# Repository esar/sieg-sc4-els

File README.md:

# sieg-sc4-els
SIEG SC4 Electronic Lead Screw

This is an electronic lead screw controller designed for the SIEG SC4 lathe, though it would also work fine for others.

This repo contains the Kicad files for the controller PCB and the firmware.

See https://hacks.esar.org.uk/sieg-sc4-electronic-lead-screw/ for more details

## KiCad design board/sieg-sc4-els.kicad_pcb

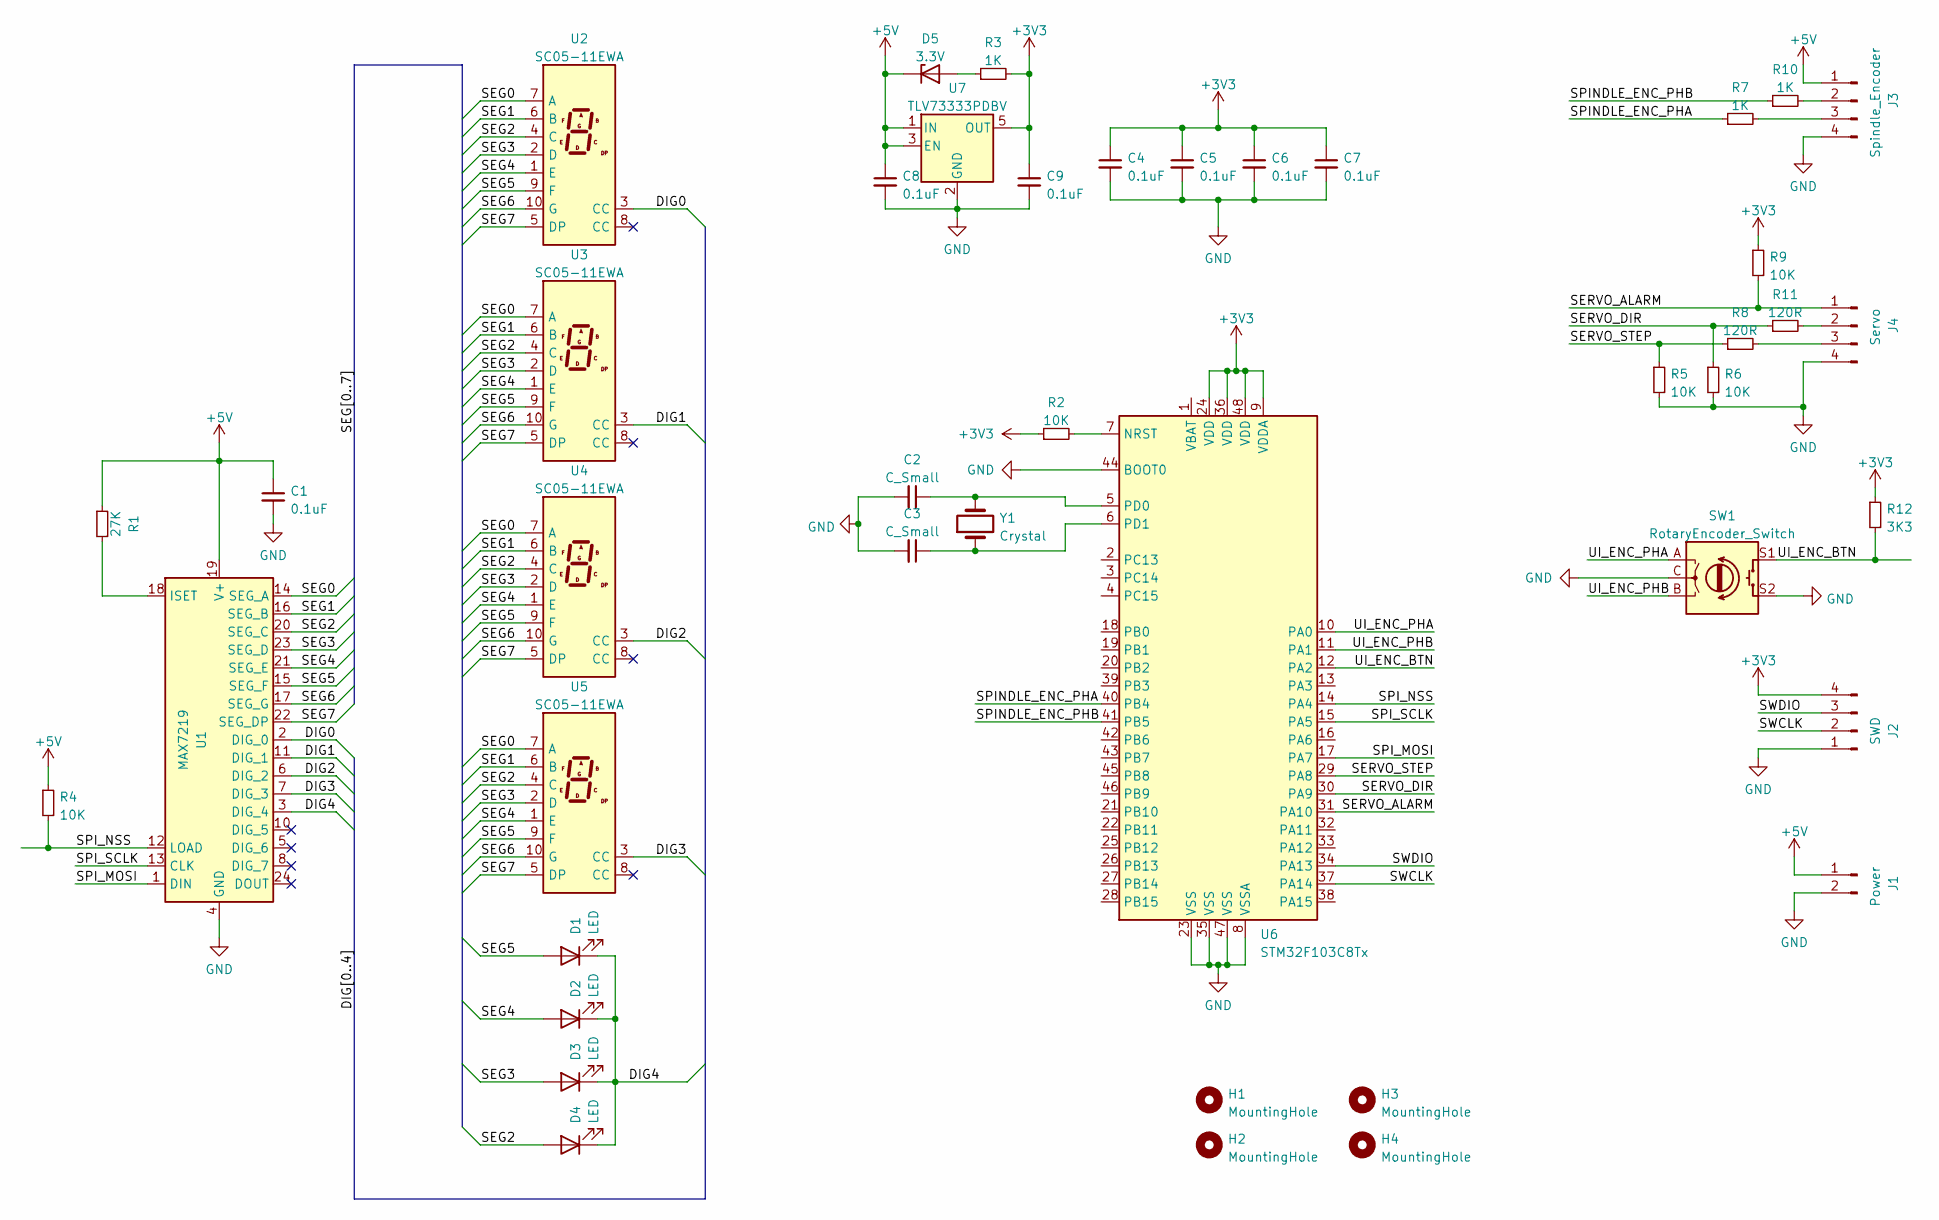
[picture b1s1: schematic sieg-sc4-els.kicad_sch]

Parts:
C1, C4, C5, C6, C7, C8, C9: 0.1uF; C_0603_1608Metric
C2, C3: C_Small; C_0603_1608Metric
D1, D2, D3, D4: LED; LED_D3.0mm
D5: 3.3V; D_SOD-323
H1, H2, H3, H4: MountingHole; MountingHole_3.2mm_M3
J1: Power; JST_XH_B2B-XH-A_1x02_P2.50mm_Vertical
J2: SWD; JST_XH_B4B-XH-A_1x04_P2.50mm_Vertical
J3: Spindle_Encoder; JST_XH_B4B-XH-A_1x04_P2.50mm_Vertical
J4: Servo; JST_XH_B4B-XH-A_1x04_P2.50mm_Vertical
R1: 27K; R_0603_1608Metric
R2, R4, R5, R6, R9: 10K; R_0603_1608Metric
R3, R7, R10: 1K; R_0603_1608Metric
R8, R11: 120R; R_0603_1608Metric
R12: 3K3; R_0603_1608Metric
SW1: RotaryEncoder_Switch; RotaryEncoder_Alps_EC11E-Switch_Vertical_H20mm
U1: MAX7219; SOIC-24W_7.5x15.4mm_P1.27mm
U2, U3, U4, U5: SC05-11EWA; D1X8K
U6: STM32F103C8Tx; LQFP-48_7x7mm_P0.5mm
U7: TLV73333PDBV; SOT-23-5
Y1: Crystal; Crystal_SMD_SeikoEpson_MA505-2Pin_12.7x5.1mm

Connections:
+3V3: C4.1, C5.1, C6.1, C7.1, C9.1, J2.4, R2.1, R3.2, R9.1, R12.1, U6.9 (VDDA), U6.24 (VDD), U6.36 (VDD), U6.48 (VDD), U7.5 (OUT)
+5V: C1.1, C8.1, D5.1 (K), J1.1, J3.1, R1.1, R4.1, U1.19 (V+), U7.1 (IN), U7.3 (EN)
/DIG0: U1.2 (DIG_0), U2.3 (CC)
/DIG1: U1.11 (DIG_1), U3.3 (CC)
/DIG2: U1.6 (DIG_2), U4.3 (CC)
/DIG3: U1.7 (DIG_3), U5.3 (CC)
/DIG4: D1.1 (K), D2.1 (K), D3.1 (K), D4.1 (K), U1.3 (DIG_4)
/SEG0: U1.14 (SEG_A), U2.7 (A), U3.7 (A), U4.7 (A), U5.7 (A)
/SEG1: U1.16 (SEG_B), U2.6 (B), U3.6 (B), U4.6 (B), U5.6 (B)
/SEG2: D4.2 (A), U1.20 (SEG_C), U2.4 (C), U3.4 (C), U4.4 (C), U5.4 (C)
/SEG3: D3.2 (A), U1.23 (SEG_D), U2.2 (D), U3.2 (D), U4.2 (D), U5.2 (D)
/SEG4: D2.2 (A), U1.21 (SEG_E), U2.1 (E), U3.1 (E), U4.1 (E), U5.1 (E)
/SEG5: D1.2 (A), U1.15 (SEG_F), U2.9 (F), U3.9 (F), U4.9 (F), U5.9 (F)
/SEG6: U1.17 (SEG_G), U2.10 (G), U3.10 (G), U4.10 (G), U5.10 (G)
/SEG7: U1.22 (SEG_DP), U2.5 (DP), U3.5 (DP), U4.5 (DP), U5.5 (DP)
/SERVO_ALARM: J4.1, R9.2, U6.31 (PA10)
/SERVO_DIR: R6.1, R11.1, U6.30 (PA9)
/SERVO_STEP: R5.1, R8.1, U6.29 (PA8)
/SPINDLE_ENC_PHA: R7.1, U6.40 (PB4)
/SPINDLE_ENC_PHB: R10.1, U6.41 (PB5)
/SPI_MOSI: U1.1 (DIN), U6.17 (PA7)
/SPI_NSS: R4.2, U1.12 (LOAD), U6.14 (PA4)
/SPI_SCLK: U1.13 (CLK), U6.15 (PA5)
/SWCLK: J2.2, U6.37 (PA14)
/SWDIO: J2.3, U6.34 (PA13)
/UI_ENC_BTN: R12.2, SW1.S1, U6.12 (PA2)
/UI_ENC_PHA: SW1.A, U6.10 (PA0)
/UI_ENC_PHB: SW1.B, U6.11 (PA1)
GND: C1.2, C2.2, C3.2, C4.2, C5.2, C6.2, C7.2, C8.2, C9.2, J1.2, J2.1, J3.4, J4.4, R5.2, R6.2, SW1.C, SW1.S2, U1.4 (GND), U1.9 (GND), U6.8 (VSSA), U6.23 (VSS), U6.35 (VSS), U6.44 (BOOT0), U6.47 (VSS), U7.2 (GND)
unnamed: C2.1, U6.5 (PD0), Y1.2
unnamed: C3.1, U6.6 (PD1), Y1.1
unnamed: D5.2 (A), R3.1
unnamed: J3.2, R10.2
unnamed: J3.3, R7.2
unnamed: J4.2, R11.2
unnamed: J4.3, R8.2
unnamed: R1.2, U1.18 (ISET)
unnamed: R2.2, U6.7 (NRST)

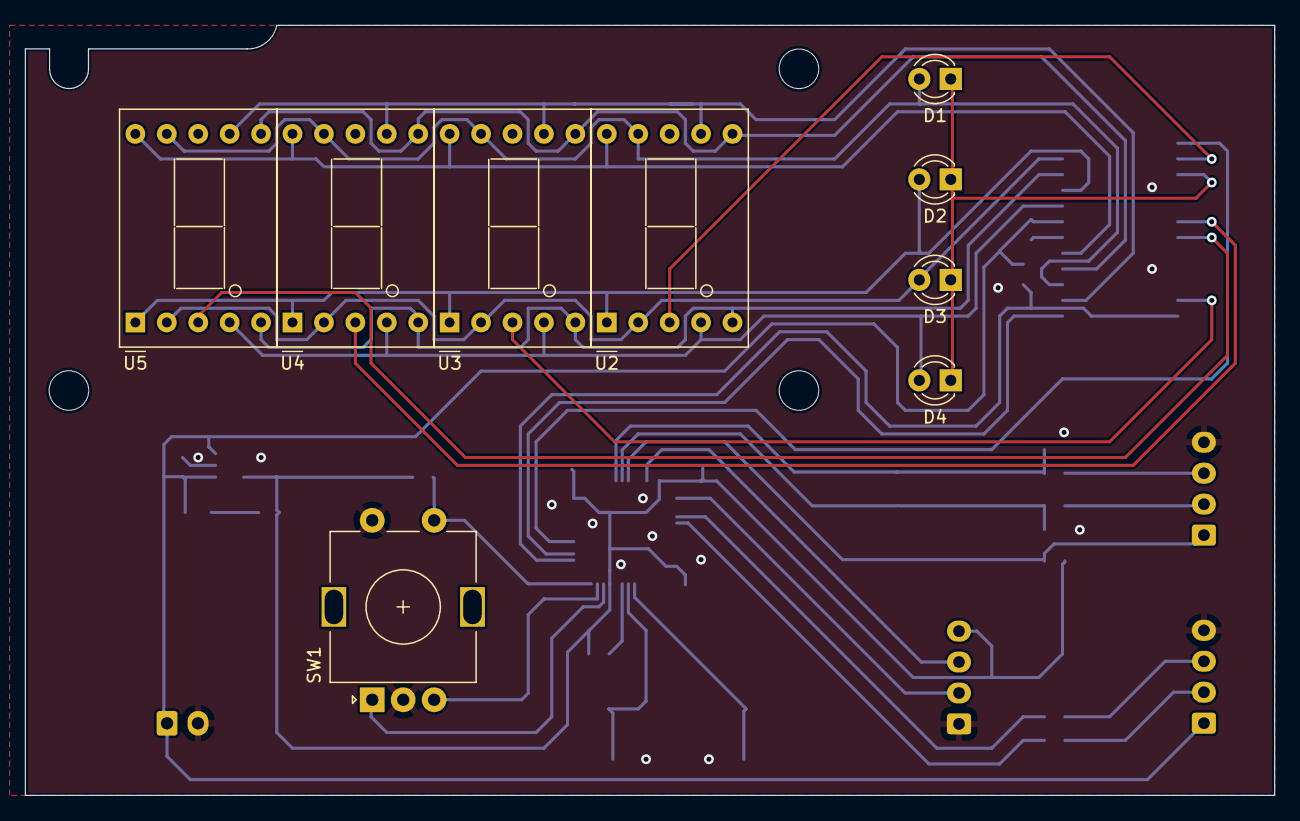
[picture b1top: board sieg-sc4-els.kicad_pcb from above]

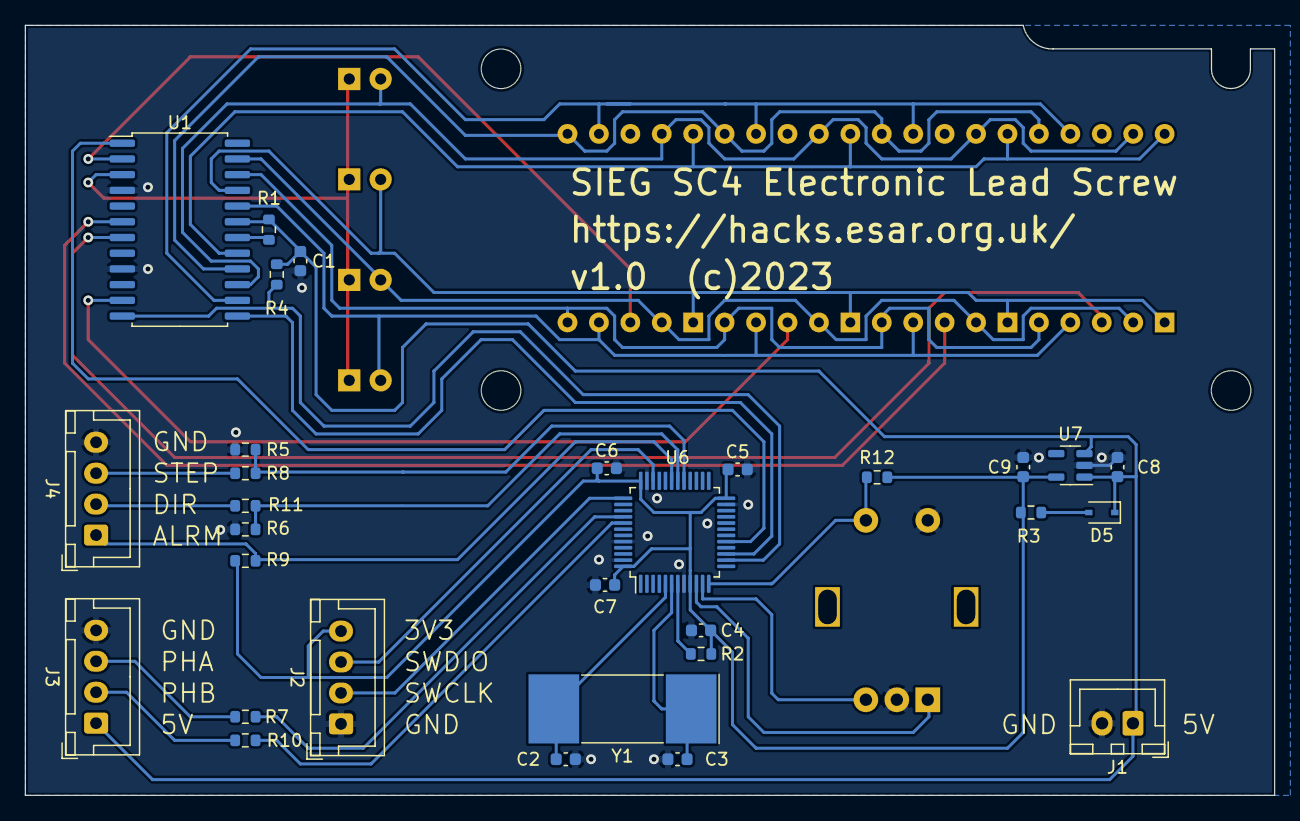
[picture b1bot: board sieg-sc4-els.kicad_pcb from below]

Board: 2 copper layers, 101.0 x 62.2 mm, 42 parts (30 on the bottom side), 38 nets.

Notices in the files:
board/sieg-sc4-els.kicad_pcb:
v1.0  (c)2023
